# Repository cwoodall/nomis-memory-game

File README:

# Nomis Memory Game

A Simon-like Memory Game!

2011 (c) Christopher Woodall
MIT License

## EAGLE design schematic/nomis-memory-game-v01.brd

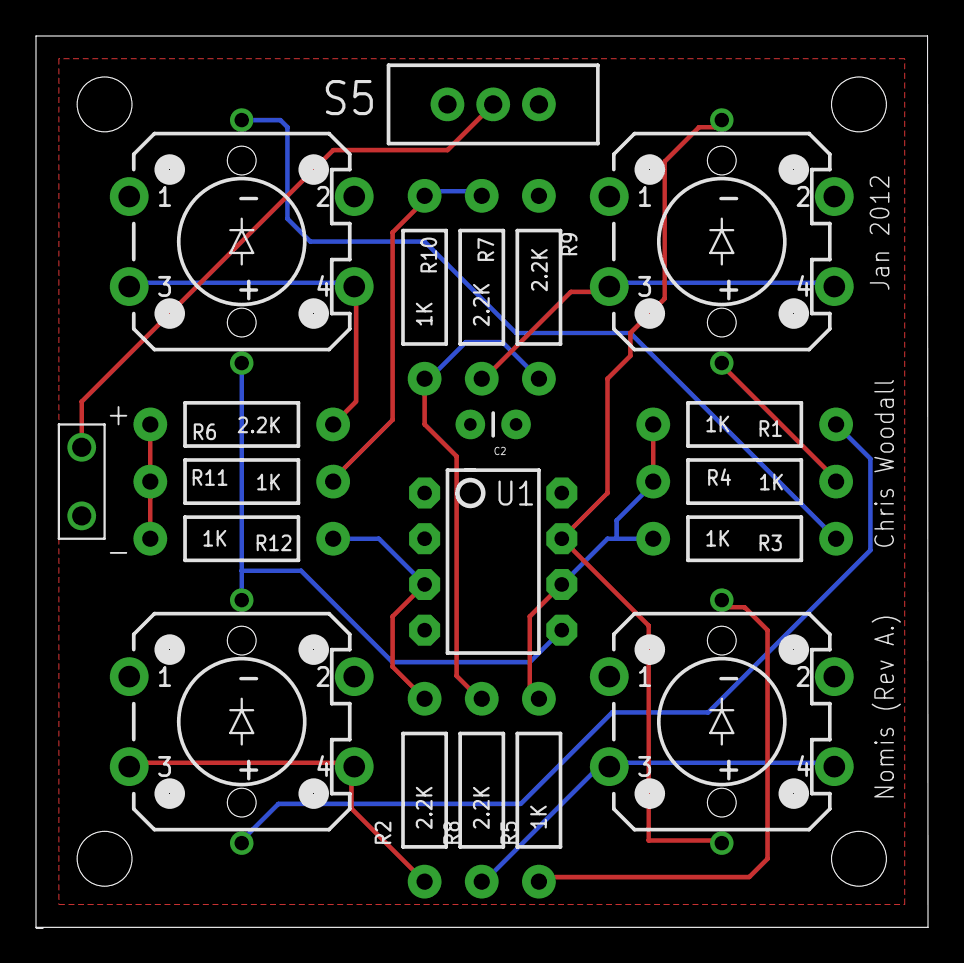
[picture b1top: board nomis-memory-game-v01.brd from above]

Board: 2 copper layers, 49.6 x 49.5 mm, 24 parts (0 on the bottom side), 18 nets.

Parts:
BATT1: 2AA External Connector; 1X02_BIG
C2: .1uF; CAP-PTH-SMALL
JP1, JP2, JP3, JP4: STAND-OFFTIGHT; STAND-OFF-TIGHT
R1, R3, R4, R5, R10, R11, R12: 1K; AXIAL-0.4
R2, R6, R7, R8, R9: 2.2K; AXIAL-0.4
S1, S2, S3, S4: SWITCH-MOMENTARY-LED-SPLIT; TACTILE-PTH-LED-12MM
S5: SWITCH-SPDT
U1: ATTINY85-DIP8; DIP08

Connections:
GND: BATT1.P$1, C2.2, R9.P$1, U1.4
unnamed: R3.P$2, S3.A
unnamed: R4.P$1, S2.C
unnamed: R5.P$1, S1.A
unnamed: R1.P$2, S4.C
unnamed: R1.P$1, R3.P$1, R4.P$2, R5.P$2, U1.6
unnamed: S1.C, S2.A, U1.7
unnamed: S3.C, S4.A, U1.5
unnamed: R8.P$2, R9.P$2, R10.P$1
unnamed: R7.P$2, R10.P$2, R11.P$1
unnamed: BATT1.P$2, S5.2
unnamed: R2.P$2, R12.P$2, U1.3
unnamed: R2.P$1, S4.3, S4.4
unnamed: R6.P$1, S3.3, S3.4
unnamed: R7.P$1, S2.3, S2.4
unnamed: R8.P$1, S1.3, S1.4
unnamed: R6.P$2, R11.P$2, R12.P$1
VCC: C2.1, S1.1, S1.2, S2.1, S2.2, S3.1, S3.2, S4.1, S4.2, S5.1, U1.1, U1.8

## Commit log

2011-12-29 Intial commit
2011-12-29 cleaning up
2011-12-30 Added new player mode, no big bugs
2011-12-30 Got the whole thing working! A few bugs still (sometimes it will register a hit as a miss, but I can't get this to happen reliably so I can't troubleshoot it). Need to clean up code
2011-12-30 Readme fixes
2011-12-31 Edited README.md and started Schematic
2011-12-31 Added Schematic File
2012-01-02 Added PCB board layout and edited the schematic a bit to fit the PCB board. Need to clean up a few things yet
2012-01-05 Fixed schematic inconsistencies and PCB... Too bad I ordered the boards already. Trying to fix that
2012-01-09 fixed up schematics and revised code a bit. Nothing major
2012-01-09 Cleaned up directory
2012-01-09 Updated pcb gerber files. Review PCB once more before sending out to Seeed again (first run had a major error in it :/)
2012-01-09 .DS_Store is still here for some reason... Trying to delete it

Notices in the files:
parts and their libraries:
SparkFun: Licensing: CC v3.0 Share-Alike You are welcome to use this library for commercial purposes.
